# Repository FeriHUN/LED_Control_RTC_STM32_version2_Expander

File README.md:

# LED_Control_RTC_STM32_version2_Expander
I/O Expander board for LED_Control_RTC_STM32_version2

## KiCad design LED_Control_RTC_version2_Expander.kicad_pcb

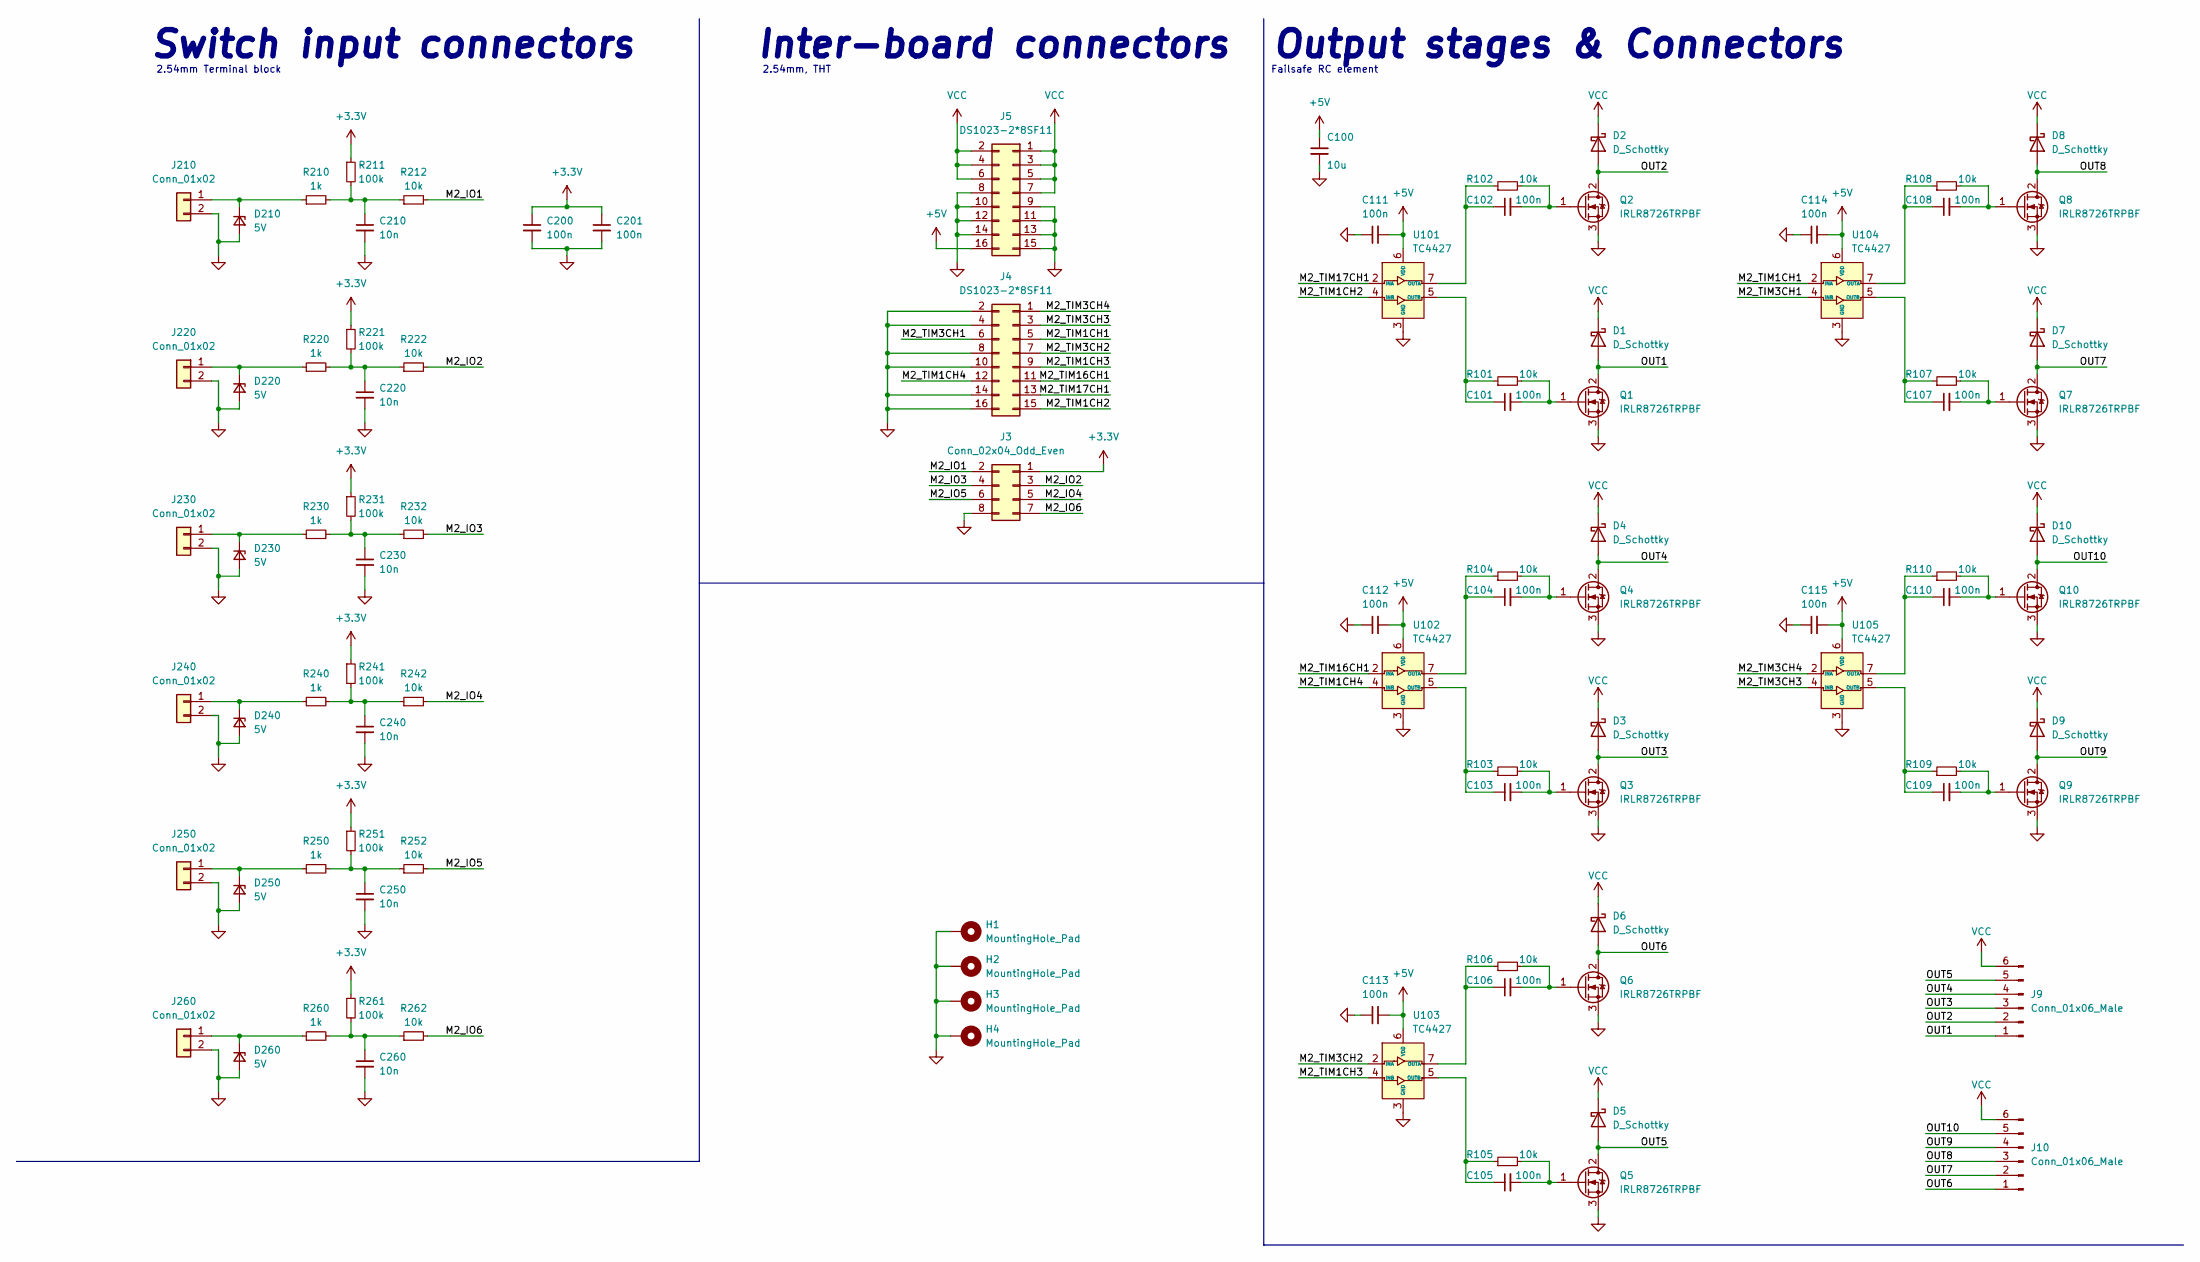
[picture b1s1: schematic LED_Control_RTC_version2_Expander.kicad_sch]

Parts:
C100: 10u; R_1206_3216Metric
C101, C102, C103, C104, C105, C106, C107, C108, C109, C110, C111, C112, C113, C114, C115, C200, C201: 100n; C_0402_1005Metric
C210, C220, C230, C240, C250, C260: 10n; C_0402_1005Metric
D1, D2, D3, D4, D5, D6, D7, D8, D9, D10: D_Schottky; D_SMA
D210, D220, D230, D240, D250, D260: 5V; D_SOD-323
H1, H2, H3, H4: MountingHole_Pad; MountingHole_3.2mm_M3_Pad_Via
J3: Conn_02x04_Odd_Even; PinSocket_2x04_P2.54mm_Vertical
J4, J5: DS1023-2*8SF11; PinSocket_2x08_P2.54mm_Vertical
J9, J10: Conn_01x06_Male; PhoenixContact_MCV_1,5_6-GF-3.81_1x06_P3.81mm_Vertical_Thre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
J210, J220, J230, J240, J250, J260: Conn_01x02; DB2ERC-2.54-2P-GN
Q1, Q2, Q3, Q4, Q5, Q6, Q7, Q8, Q9, Q10: IRLR8726TRPBF; TO-252-2
R101, R102, R103, R104, R105, R106, R107, R108, R109, R110, R212, R222, R232, R242, R252, R262: 10k; R_0402_1005Metric
R210, R220, R230, R240, R250, R260: 1k; R_0402_1005Metric
R211, R221, R231, R241, R251, R261: 100k; R_0402_1005Metric
U101, U102, U103, U104, U105: TC4427; SOIC-8_3.9x4.9mm_P1.27mm

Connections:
+3V3: C200.1, C201.1, J3.1, R211.1, R221.1, R231.1, R241.1, R251.1, R261.1
+5V: C100.1, C111.2, C112.2, C113.2, C114.2, C115.2, J5.16, U101.6 (VDD), U102.6 (VDD), U103.6 (VDD), U104.6 (VDD), U105.6 (VDD)
/M2_IO1: J3.2, R212.2
/M2_IO2: J3.3, R222.2
/M2_IO3: J3.4, R232.2
/M2_IO4: J3.5, R242.2
/M2_IO5: J3.6, R252.2
/M2_IO6: J3.7, R262.2
/M2_TIM1CH1: J4.5, U104.2 (INA)
/M2_TIM1CH2: J4.15, U101.4 (INB)
/M2_TIM1CH3: J4.9, U103.4 (INB)
/M2_TIM1CH4: J4.12, U102.4 (INB)
/M2_TIM3CH1: J4.6, U104.4 (INB)
/M2_TIM3CH2: J4.7, U103.2 (INA)
/M2_TIM3CH3: J4.3, U105.4 (INB)
/M2_TIM3CH4: J4.1, U105.2 (INA)
/M2_TIM16CH1: J4.11, U102.2 (INA)
/M2_TIM17CH1: J4.13, U101.2 (INA)
/OUT1: D1.2 (A), J9.1, Q1.2 (D)
/OUT2: D2.2 (A), J9.2, Q2.2 (D)
/OUT3: D3.2 (A), J9.3, Q3.2 (D)
/OUT4: D4.2 (A), J9.4, Q4.2 (D)
/OUT5: D5.2 (A), J9.5, Q5.2 (D)
/OUT6: D6.2 (A), J10.1, Q6.2 (D)
/OUT7: D7.2 (A), J10.2, Q7.2 (D)
/OUT8: D8.2 (A), J10.3, Q8.2 (D)
/OUT9: D9.2 (A), J10.4, Q9.2 (D)
/OUT10: D10.2 (A), J10.5, Q10.2 (D)
GND: C100.2, C111.1, C112.1, C113.1, C114.1, C115.1, C200.2, C201.2, C210.2, C220.2, C230.2, C240.2, C250.2, C260.2, D210.2 (A), D220.2 (A), D230.2 (A), D240.2 (A), D250.2 (A), D260.2 (A), H1.1, H2.1, H3.1, H4.1, J3.8, J4.2, J4.4, J4.8, J4.10, J4.14, J4.16, J5.8, J5.9, J5.10, J5.11, J5.12, J5.13, J5.14, J5.15, J210.2, J220.2, J230.2, J240.2, J250.2, J260.2, Q1.3 (S), Q2.3 (S), Q3.3 (S), Q4.3 (S), Q5.3 (S), Q6.3 (S), Q7.3 (S), Q8.3 (S), Q9.3 (S), Q10.3 (S), U101.3 (GND), U102.3 (GND), U103.3 (GND), U104.3 (GND), U105.3 (GND)
unnamed: C101.1, R101.1, U101.5 (OUTB)
unnamed: C101.2, Q1.1 (G), R101.2
unnamed: C102.1, R102.1, U101.7 (OUTA)
unnamed: C102.2, Q2.1 (G), R102.2
unnamed: C103.1, R103.1, U102.5 (OUTB)
unnamed: C103.2, Q3.1 (G), R103.2
unnamed: C104.1, R104.1, U102.7 (OUTA)
unnamed: C104.2, Q4.1 (G), R104.2
unnamed: C105.1, R105.1, U103.5 (OUTB)
unnamed: C105.2, Q5.1 (G), R105.2
unnamed: C106.1, R106.1, U103.7 (OUTA)
unnamed: C106.2, Q6.1 (G), R106.2
unnamed: C107.1, R107.1, U104.5 (OUTB)
unnamed: C107.2, Q7.1 (G), R107.2
unnamed: C108.1, R108.1, U104.7 (OUTA)
unnamed: C108.2, Q8.1 (G), R108.2
unnamed: C109.1, R109.1, U105.5 (OUTB)
unnamed: C109.2, Q9.1 (G), R109.2
unnamed: C110.1, R110.1, U105.7 (OUTA)
unnamed: C110.2, Q10.1 (G), R110.2
unnamed: C210.1, R210.2, R211.2, R212.1
unnamed: C220.1, R220.2, R221.2, R222.1
unnamed: C230.1, R230.2, R231.2, R232.1
unnamed: C240.1, R240.2, R241.2, R242.1
unnamed: C250.1, R250.2, R251.2, R252.1
unnamed: C260.1, R260.2, R261.2, R262.1
unnamed: D210.1 (K), J210.1, R210.1
unnamed: D220.1 (K), J220.1, R220.1
unnamed: D230.1 (K), J230.1, R230.1
unnamed: D240.1 (K), J240.1, R240.1
unnamed: D250.1 (K), J250.1, R250.1
unnamed: D260.1 (K), J260.1, R260.1
VCC: D1.1 (K), D2.1 (K), D3.1 (K), D4.1 (K), D5.1 (K), D6.1 (K), D7.1 (K), D8.1 (K), D9.1 (K), D10.1 (K), J5.1, J5.2, J5.3, J5.4, J5.5, J5.6, J5.7, J9.6, J10.6

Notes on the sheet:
Failsafe RC element
Inter-board connectors
Switch input connectors
2.54mm Terminal block
2.54mm, THT
Output stages & Connectors

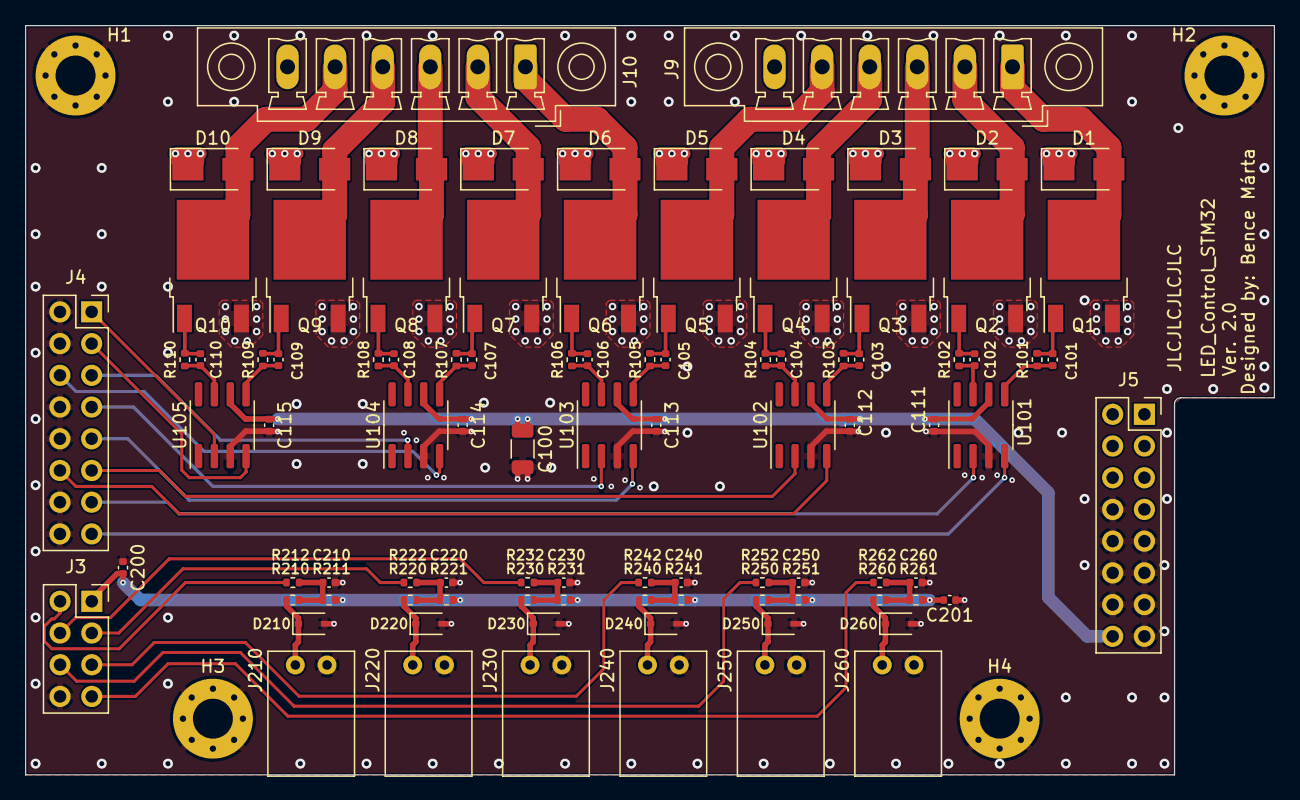
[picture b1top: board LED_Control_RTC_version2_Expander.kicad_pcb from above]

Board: 4 copper layers, 100.0 x 60.0 mm, 98 parts (0 on the bottom side), 62 nets.

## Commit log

2022-09-13 Added ESD protection to switch inputs and filled planes
2022-09-13 Finished design
2022-09-16 Ready for prod
